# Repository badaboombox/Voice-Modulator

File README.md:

# Voice Modulator

The original project contains the fully routed 95 x 65 mm board. [PCB layout and checks](PCB_LAYOUT.md)

[JLCPCB quote files](production/README.md) · [Schematic and board screenshots](screenshots/README.md)

**Rev A.2 electrical plan locked for schematic capture — 2026-11-21.**

- [SCHEMATIC_GUIDE.md](SCHEMATIC_GUIDE.md): fixed architecture, six
  sheets, operating modes, power sequencing, layout constraints and acceptance work.
- [IC_CONNECTIONS.md](IC_CONNECTIONS.md): draw one sheet at a time. Pin tables
  list nets; each passive value and connection appears once beside its associated
  component. All 15 IC/protection devices and inter-sheet ports are covered.

The screenshot components remain the foundation. The abbreviated flash ordering
code is resolved to W25Q128JVSIQ; the required speaker amp is PAM8403DR (SOP-16). The added codec,
analog-switch ring modulator, oscillator, flash and protection implement Tiers 2/3
and replay of recorded speech through the analog effect.

| Constraint | Locked decision |
| --- | --- |
| PCB | 95 x 65 mm, four layers, 1.6-mm FR-4 |
| Effect | Analog metallic ring modulation, tone and dry/wet blend |
| Audio | 32 ksample/s, 16-bit; one 10-second dry recording slot |
| Monitoring | Headphones live; armed internal speaker for recorded playback |
| Power | USB 2.0 host-powered, 500-mA configuration |
| Budget | $185 allocation, under-$200 landed-order requirement |

Schematic capture and PCB routing are complete. The project includes the files for a manufacturing estimate. Firmware, hardware validation, and a vendor price remain open.

Rev A.2 retains U6 TLV320AIC3104IRHBR after comparison with AIC3204 and adopts
D1 USBLC6-2SC6 for USB ESD protection, matching the part already in the schematic.

Rev A.2 corrects U12 to the user-specified PAM8403DR already present in KiCad.
Its 16-pin table includes one-channel speaker wiring, input attenuation, VREF
bypass and mute/shutdown control.

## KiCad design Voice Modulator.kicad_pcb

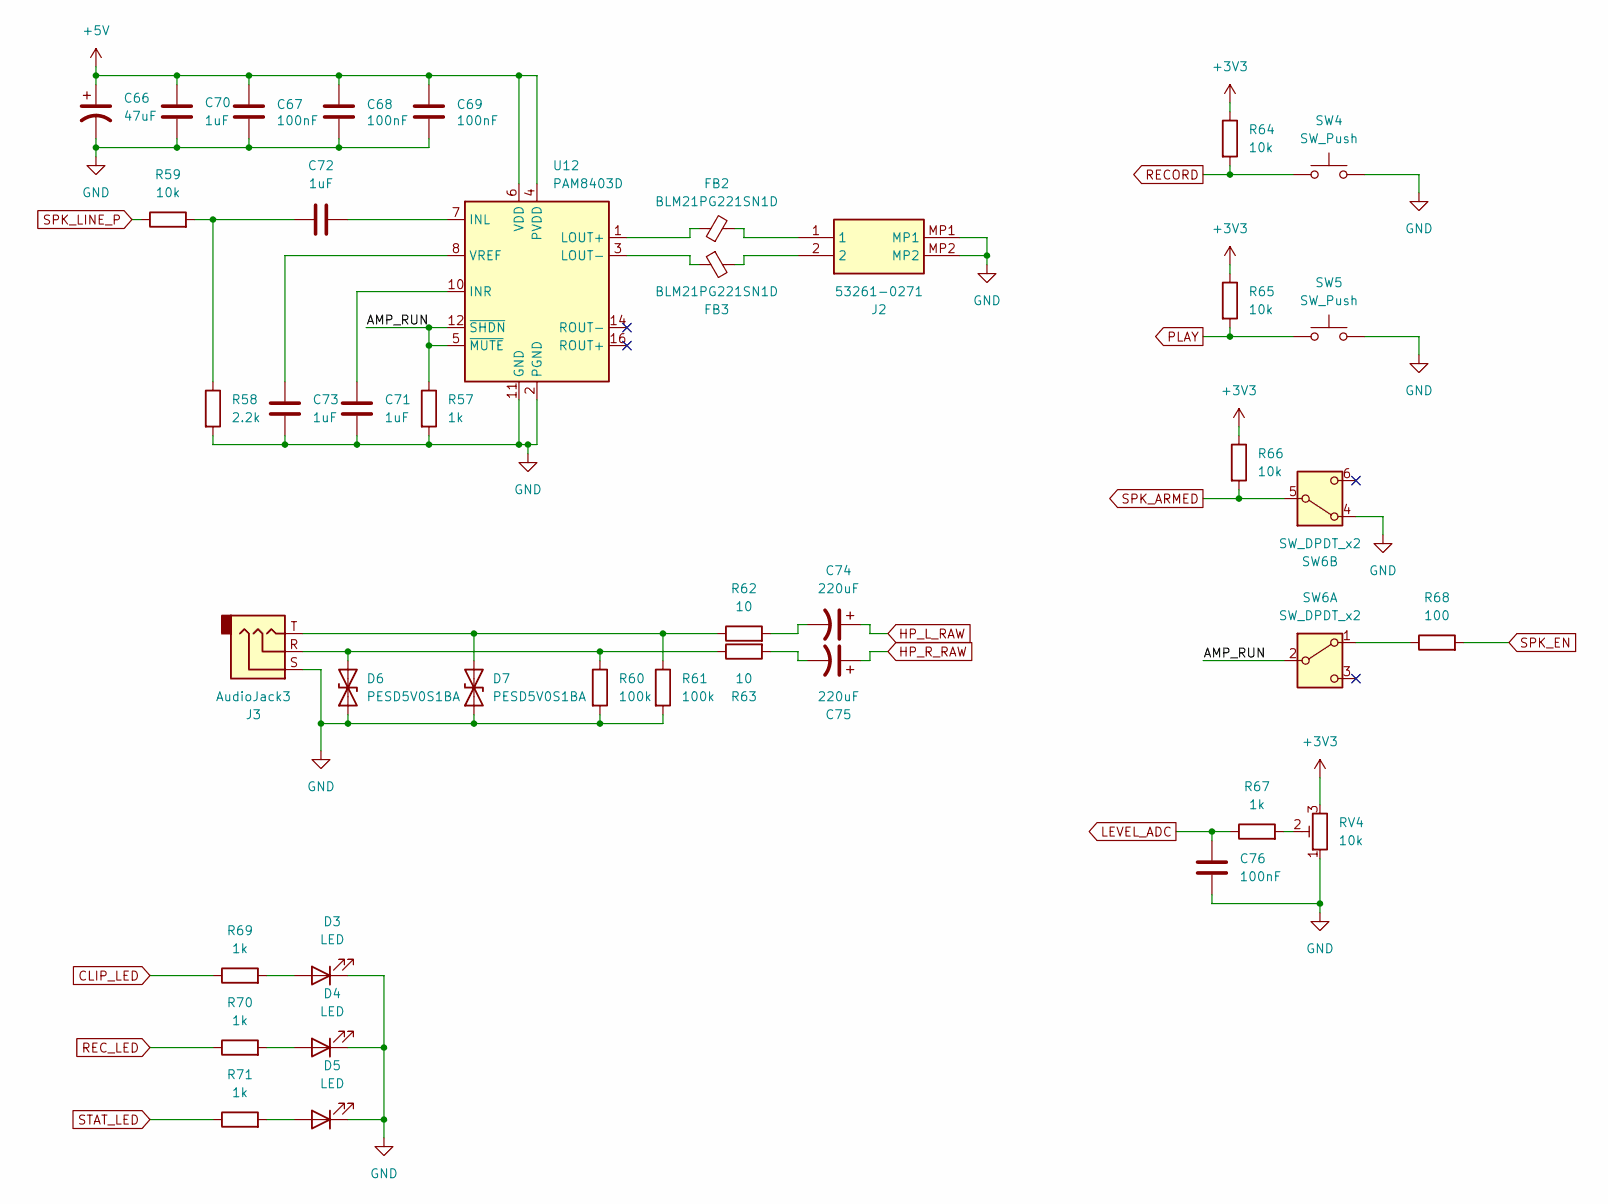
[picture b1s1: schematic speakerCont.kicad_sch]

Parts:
C66: 47uF; CP_Radial_D5.0mm_P2.00mm
C67, C68, C69, C76: 100nF; C_0402_1005Metric
C70, C71, C72, C73: 1uF; C_0805_2012Metric
C74, C75: 220uF; CP_Radial_D6.3mm_P2.50mm
D3, D4, D5: LED; LED_0805_2012Metric
D6, D7: PESD5V0S1BA; D_SOD-323
FB2, FB3: BLM21PG221SN1D; L_0805_2012Metric
J2: 53261-0271; 532610271; Manufacturer_Part_Number 53261-0271; Mouser Part Number 538-53261-0271
J3: AudioJack3; Jack_3.5mm_CUI_SJ-3523-SMT_Horizontal
R57, R67, R69, R70, R71: 1k; R_0402_1005Metric
R58: 2.2k; R_0402_1005Metric
R59, R64, R65, R66: 10k; R_0402_1005Metric
R60, R61: 100k; R_0402_1005Metric
R62, R63: 10; R_0402_1005Metric
R68: 100; R_0402_1005Metric
RV4: 10k; Potentiometer_Bourns_PTV09A-1_Single_Vertical
SW4, SW5: SW_Push; SW_PUSH_6mm_H4.3mm
SW6: SW_DPDT_x2; SW_E-Switch_EG2219_DPDT_Angled
U12: PAM8403D; SOIC-16_3.9x9.9mm_P1.27mm

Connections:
+3V3: R64.1, R65.1, R66.1, RV4.3; also elsewhere on the board
+5V: C66.1, C67.1, C68.1, C69.1, C70.1, U12.4 (PVDD), U12.6 (VDD), U12.13 (PVDD); also elsewhere on the board
/Speaker + Controls/AMP_RUN: R57.1, SW6.2 (B), U12.5 (~MUTE), U12.12 (~SHDN)
CLIP_LED: R69.1; also elsewhere on the board
GND: C66.2, C67.2, C68.2, C69.2, C70.2, C71.2, C73.2, C76.2, D3.1 (K), D4.1 (K), D5.1 (K), D6.1 (A1), D7.1 (A1), J2.MP1, J2.MP2, J3.S, R57.2, R58.2, R60.2, R61.2, RV4.1, SW4.2, SW5.2, SW6.4 (A), U12.2 (PGND), U12.11 (GND), U12.15 (PGND); also elsewhere on the board
HP_L_RAW: C74.1; also elsewhere on the board
HP_R_RAW: C75.1; also elsewhere on the board
LEVEL_ADC: C76.1, R67.1; also elsewhere on the board
unnamed: C72.1, R58.1, R59.2
unnamed: C74.2, R62.2
unnamed: C75.2, R63.2
unnamed: D3.2 (A), R69.2
unnamed: D4.2 (A), R70.2
unnamed: D5.2 (A), R71.2
unnamed: D6.2 (A2), J3.R, R60.1, R63.1
unnamed: D7.2 (A2), J3.T, R61.1, R62.1
unnamed: FB2.2, J2.1
unnamed: FB3.2, J2.2
unnamed: R67.2, RV4.2
unnamed: R68.1, SW6.1 (A)
unnamed: C72.2, U12.7 (INL)
unnamed: C71.1, U12.10 (INR)
unnamed: FB2.1, U12.1 (LOUT+)
unnamed: FB3.1, U12.3 (LOUT-)
unnamed: C73.1, U12.8 (VREF)
PLAY: R65.2, SW5.1; also elsewhere on the board
RECORD: R64.2, SW4.1; also elsewhere on the board
REC_LED: R70.1; also elsewhere on the board
SPK_ARMED: R66.2, SW6.5 (B); also elsewhere on the board
SPK_EN: R68.2; also elsewhere on the board
SPK_LINE_P: R59.1; also elsewhere on the board
STAT_LED: R71.1; also elsewhere on the board

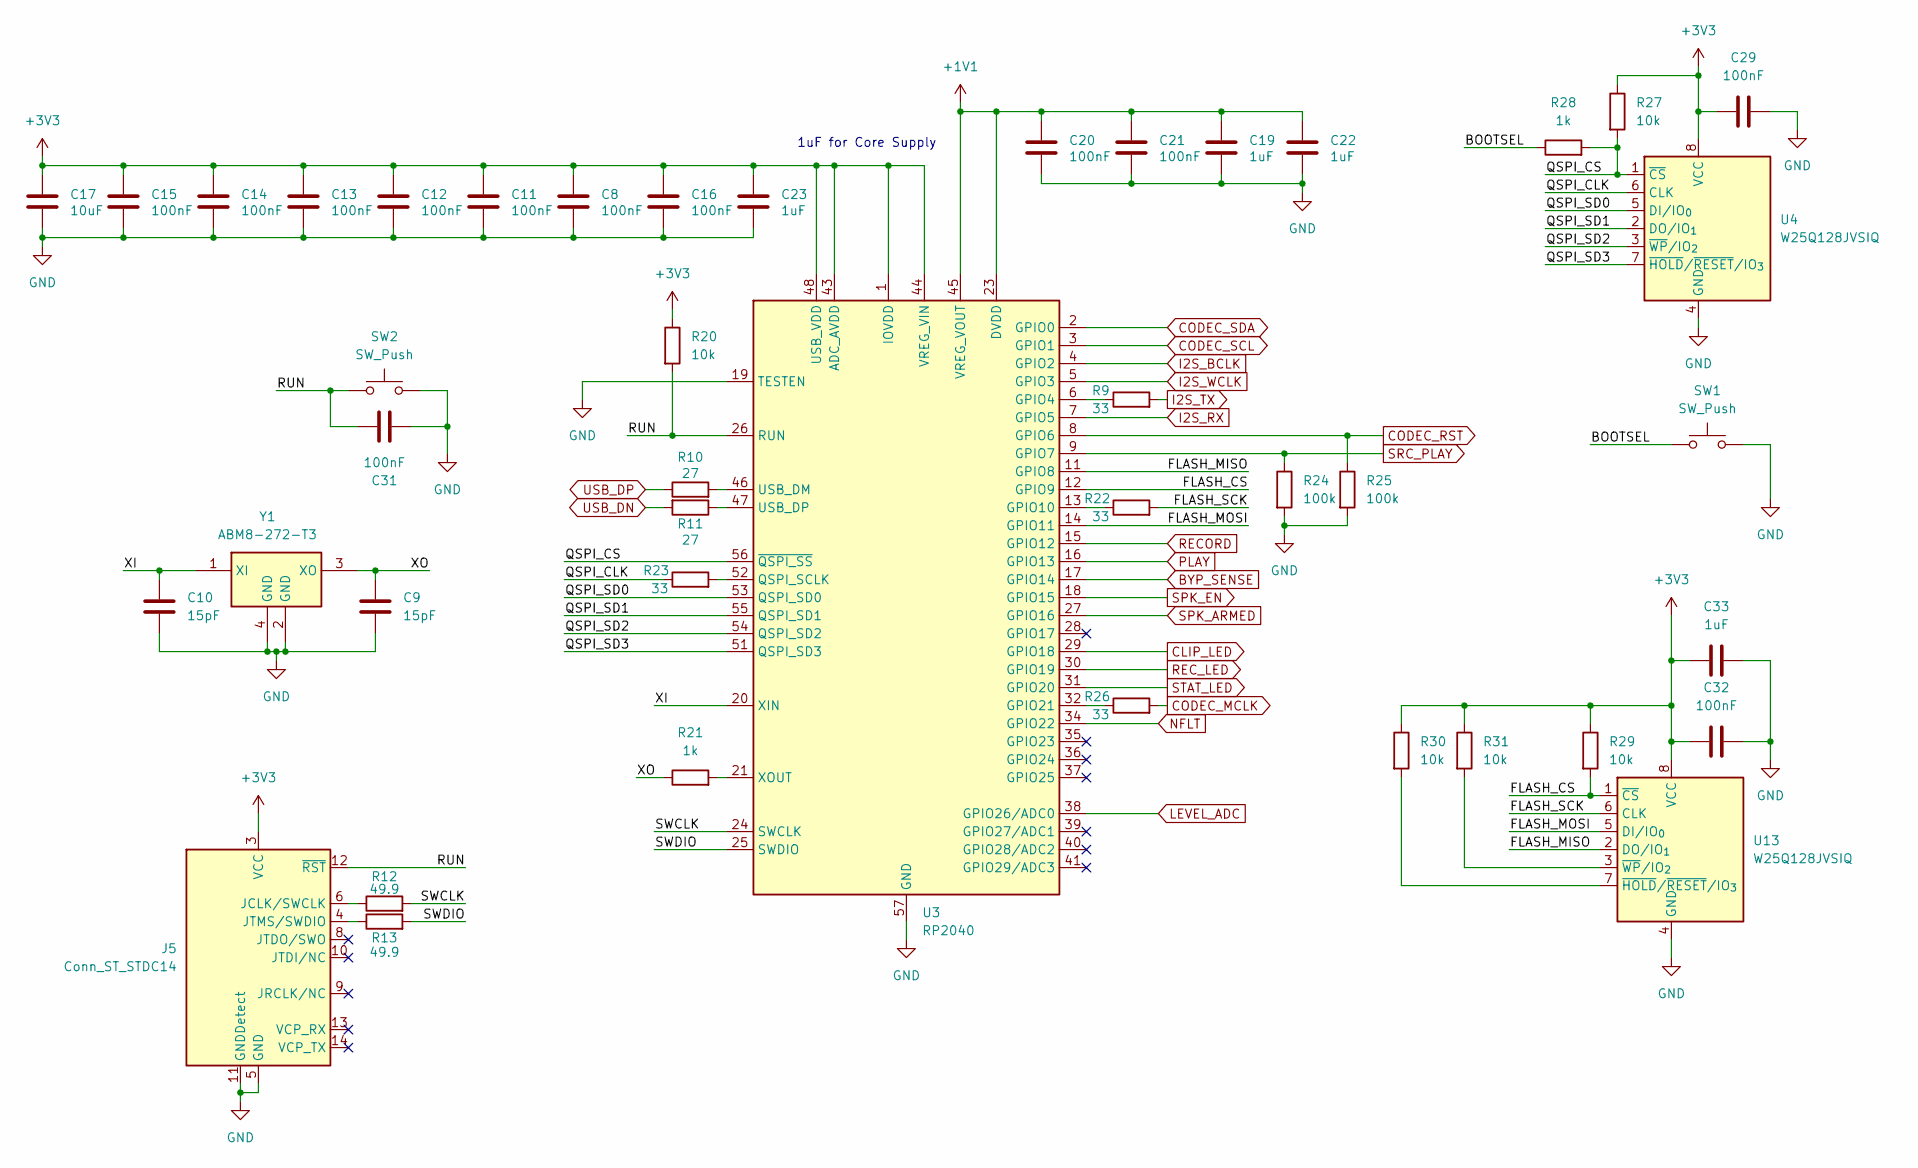
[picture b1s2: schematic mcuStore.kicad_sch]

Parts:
C8, C11, C12, C13, C14, C15, C16, C20, C21, C29, C31, C32: 100nF; C_0402_1005Metric
C9, C10: 15pF; C_0402_1005Metric
C17: 10uF; C_1206_3216Metric
C19, C22, C23, C33: 1uF; C_0805_2012Metric
J5: Conn_ST_STDC14; PinHeader_2x07_P1.27mm_Vertical
R9, R22, R23, R26: 33; R_0402_1005Metric
R10, R11: 27; R_0402_1005Metric
R12, R13: 49.9; R_0402_1005Metric
R20, R27, R29, R30, R31: 10k; R_0402_1005Metric
R21, R28: 1k; R_0402_1005Metric
R24, R25: 100k; R_0402_1005Metric
SW1, SW2: SW_Push; SW_PUSH_6mm_H4.3mm
U3: RP2040; QFN-56-1EP_7x7mm_P0.4mm_EP3.2x3.2mm
U4, U13: W25Q128JVSIQ; SOIC-8_5.3x5.3mm_P1.27mm
Y1: ABM8-272-T3; ABM8272T3; Manufacturer_Part_Number ABM8-272-T3; Mouser Part Number 815-ABM8-272-T3

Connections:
+1V1: C19.1, C20.1, C21.1, C22.1, U3.23 (DVDD), U3.45 (VREG_VOUT), U3.50 (DVDD)
+3V3: C8.1, C11.1, C12.1, C13.1, C14.1, C15.1, C16.1, C17.1, C23.1, C29.1, C32.1, C33.1, J5.3 (VCC), R20.1, R27.1, R29.1, R30.1, R31.1, U3.1 (IOVDD), U3.10 (IOVDD), U3.22 (IOVDD), U3.33 (IOVDD), U3.42 (IOVDD), U3.43 (ADC_AVDD), U3.44 (VREG_VIN), U3.48 (USB_VDD), U3.49 (IOVDD), U4.8 (VCC), U13.8 (VCC); also elsewhere on the board
/MCU + Storage/BOOTSEL: R28.1, SW1.1
/MCU + Storage/FLASH_CS: R29.2, U3.12 (GPIO9), U13.1 (~CS)
/MCU + Storage/FLASH_MISO: U3.11 (GPIO8), U13.2 (DO/IO_{1})
/MCU + Storage/FLASH_MOSI: U3.14 (GPIO11), U13.5 (DI/IO_{0})
/MCU + Storage/FLASH_SCK: R22.2, U13.6 (CLK)
/MCU + Storage/QSPI_CLK: R23.1, U4.6 (CLK)
/MCU + Storage/QSPI_CS: R27.2, R28.2, U3.56 (~QSPI_SS), U4.1 (~CS)
/MCU + Storage/QSPI_SD0: U3.53 (QSPI_SD0), U4.5 (DI/IO_{0})
/MCU + Storage/QSPI_SD1: U3.55 (QSPI_SD1), U4.2 (DO/IO_{1})
/MCU + Storage/QSPI_SD2: U3.54 (QSPI_SD2), U4.3 (~WP/IO_{2})
/MCU + Storage/QSPI_SD3: U3.51 (QSPI_SD3), U4.7 (~HOLD/~RESET/IO_{3})
/MCU + Storage/RUN: C31.1, J5.12 (~RST), R20.2, SW2.1, U3.26 (RUN)
/MCU + Storage/SWCLK: R12.2, U3.24 (SWCLK)
/MCU + Storage/SWDIO: R13.2, U3.25 (SWDIO)
/MCU + Storage/XI: C10.1, U3.20 (XIN), Y1.1 (XI)
/MCU + Storage/XO: C9.1, R21.1, Y1.3 (XO)
BYP_SENSE: U3.17 (GPIO14); also elsewhere on the board
CLIP_LED: U3.29 (GPIO18); also elsewhere on the board
CODEC_MCLK: R26.2; also elsewhere on the board
CODEC_RST: R25.1, U3.8 (GPIO6); also elsewhere on the board
CODEC_SCL: U3.3 (GPIO1); also elsewhere on the board
CODEC_SDA: U3.2 (GPIO0); also elsewhere on the board
GND: C8.2, C9.2, C10.2, C11.2, C12.2, C13.2, C14.2, C15.2, C16.2, C17.2, C19.2, C20.2, C21.2, C22.2, C23.2, C29.2, C31.2, C32.2, C33.2, J5.5 (GND), J5.7 (GND), J5.11 (GNDDetect), R24.2, R25.2, SW1.2, SW2.2, U3.19 (TESTEN), U3.57 (GND), U4.4 (GND), U13.4 (GND), Y1.2 (GND), Y1.4 (GND); also elsewhere on the board
I2S_BCLK: U3.4 (GPIO2); also elsewhere on the board
I2S_RX: U3.7 (GPIO5); also elsewhere on the board
I2S_TX: R9.2; also elsewhere on the board
I2S_WCLK: U3.5 (GPIO3); also elsewhere on the board
LEVEL_ADC: U3.38 (GPIO26/ADC0); also elsewhere on the board
NFLT: U3.34 (GPIO22); also elsewhere on the board
unnamed: J5.6 (JCLK/SWCLK), R12.1
unnamed: J5.4 (JTMS/SWDIO), R13.1
unnamed: R9.1, U3.6 (GPIO4)
unnamed: R22.1, U3.13 (GPIO10)
unnamed: R26.1, U3.32 (GPIO21)
unnamed: R23.2, U3.52 (QSPI_SCLK)
unnamed: R10.2, U3.46 (USB_DM)
unnamed: R11.1, U3.47 (USB_DP)
unnamed: R21.2, U3.21 (XOUT)
unnamed: R30.2, U13.7 (~HOLD/~RESET/IO_{3})
unnamed: R31.2, U13.3 (~WP/IO_{2})
PLAY: U3.16 (GPIO13); also elsewhere on the board
RECORD: U3.15 (GPIO12); also elsewhere on the board
REC_LED: U3.30 (GPIO19); also elsewhere on the board
SPK_ARMED: U3.27 (GPIO16); also elsewhere on the board
SPK_EN: U3.18 (GPIO15); also elsewhere on the board
SRC_PLAY: R24.1, U3.9 (GPIO7); also elsewhere on the board
STAT_LED: U3.31 (GPIO20); also elsewhere on the board
USB_DN: R11.2; also elsewhere on the board
USB_DP: R10.1; also elsewhere on the board

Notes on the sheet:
1uF for Core Supply

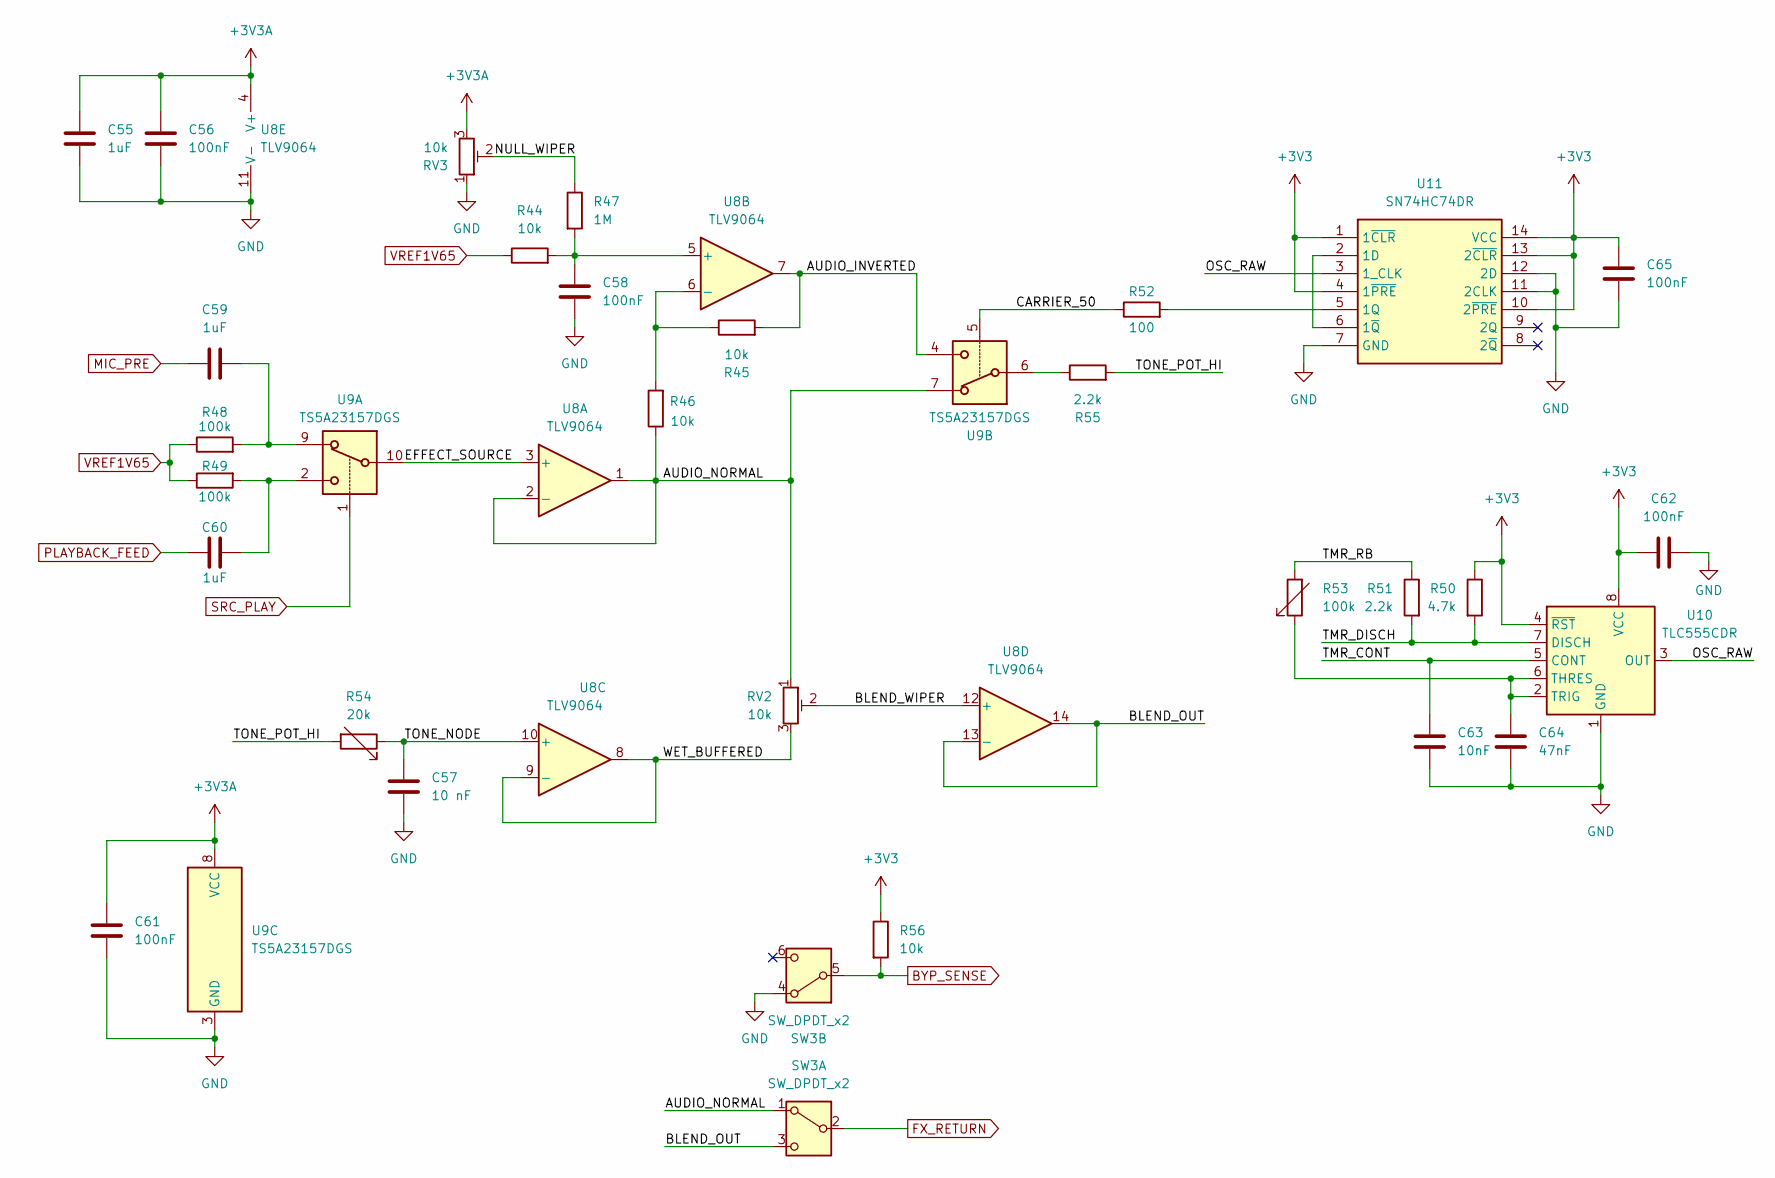
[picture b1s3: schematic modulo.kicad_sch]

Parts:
C55, C59, C60: 1uF; C_0805_2012Metric
C56, C58, C61, C62, C65: 100nF; C_0402_1005Metric
C57: 10 nF; C_0402_1005Metric
C63: 10nF; C_0402_1005Metric
C64: 47nF; C_0402_1005Metric
R44, R45, R46, R56: 10k; R_0402_1005Metric
R47: 1M; R_0402_1005Metric
R48, R49: 100k; R_0402_1005Metric
R50: 4.7k; R_0402_1005Metric
R51, R55: 2.2k; R_0402_1005Metric
R52: 100; R_0402_1005Metric
R53: 100k; Potentiometer_Bourns_PTV09A-1_Single_Vertical
R54: 20k; Potentiometer_Bourns_PTV09A-1_Single_Vertical
RV2: 10k; Potentiometer_Bourns_PTV09A-1_Single_Vertical
RV3: 10k; Potentiometer_Bourns_3296W_Vertical
SW3: SW_DPDT_x2; SW_E-Switch_EG2219_DPDT_Angled
U8: TLV9064; TSSOP-14_4.4x5mm_P0.65mm
U9: TS5A23157DGS; TSSOP-10_3x3mm_P0.5mm
U10: TLC555CDR; SOIC-8_3.9x4.9mm_P1.27mm
U11: SN74HC74DR; SOIC-14_3.9x8.7mm_P1.27mm; Manufacturer_Part_Number SN74HC74DR; Mouser Part Number 595-SN74HC74DR

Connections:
+3V3: C62.2, C65.1, R50.1, R56.1, U10.4 (~RST), U10.8 (VCC), U11.1 (1~CLR), U11.4 (1~PRE), U11.10 (2~PRE), U11.13 (2~CLR), U11.14 (VCC); also elsewhere on the board
+3V3A: C55.1, C56.1, C61.2, RV3.3, U8.4 (V+), U9.8 (VCC); also elsewhere on the board
/Modulation/AUDIO_INVERTED: R45.2, U8.7, U9.4
/Modulation/AUDIO_NORMAL: R46.1, RV2.1, SW3.1 (A), U8.1, U8.2 (-), U9.7
/Modulation/BLEND_OUT: SW3.3 (C), U8.13 (-), U8.14
/Modulation/BLEND_WIPER: RV2.2, U8.12 (+)
/Modulation/CARRIER_50: R52.1, U9.5
/Modulation/EFFECT_SOURCE: U8.3 (+), U9.10
/Modulation/NULL_WIPER: R47.1, RV3.2
/Modulation/OSC_RAW: U10.3 (OUT), U11.3 (1_CLK)
/Modulation/TMR_CONT: C63.2, U10.5 (CONT)
/Modulation/TMR_DISCH: R50.2, R51.2, U10.7 (DISCH)
/Modulation/TMR_RB: R51.1, R53.2
/Modulation/TONE_NODE: C57.1, R54.1, U8.10 (+)
/Modulation/TONE_POT_HI: R54.2, R55.2
/Modulation/WET_BUFFERED: RV2.3, U8.8, U8.9 (-)
BYP_SENSE: R56.2, SW3.5 (B); also elsewhere on the board
FX_RETURN: SW3.2 (B); also elsewhere on the board
GND: C55.2, C56.2, C57.2, C58.1, C61.1, C62.1, C63.1, C64.1, C65.2, RV3.1, SW3.4 (A), U8.11 (V-), U9.3 (GND), U10.1 (GND), U11.7 (GND), U11.11 (2CLK), U11.12 (2D); also elsewhere on the board
MIC_PRE: C59.1; also elsewhere on the board
unnamed: C59.2, R48.2, U9.9
unnamed: C60.2, R49.2, U9.2
unnamed: R55.1, U9.6
unnamed: C58.2, R44.2, R47.2, U8.5 (+)
unnamed: R45.1, R46.2, U8.6 (-)
unnamed: C64.2, R53.1, U10.2 (TRIG), U10.6 (THRES)
unnamed: U11.2 (1D), U11.6 (1~Q)
unnamed: R52.2, U11.5 (1Q)
PLAYBACK_FEED: C60.1; also elsewhere on the board
SRC_PLAY: U9.1; also elsewhere on the board
VREF1V65: R44.1, R48.1, R49.1; also elsewhere on the board

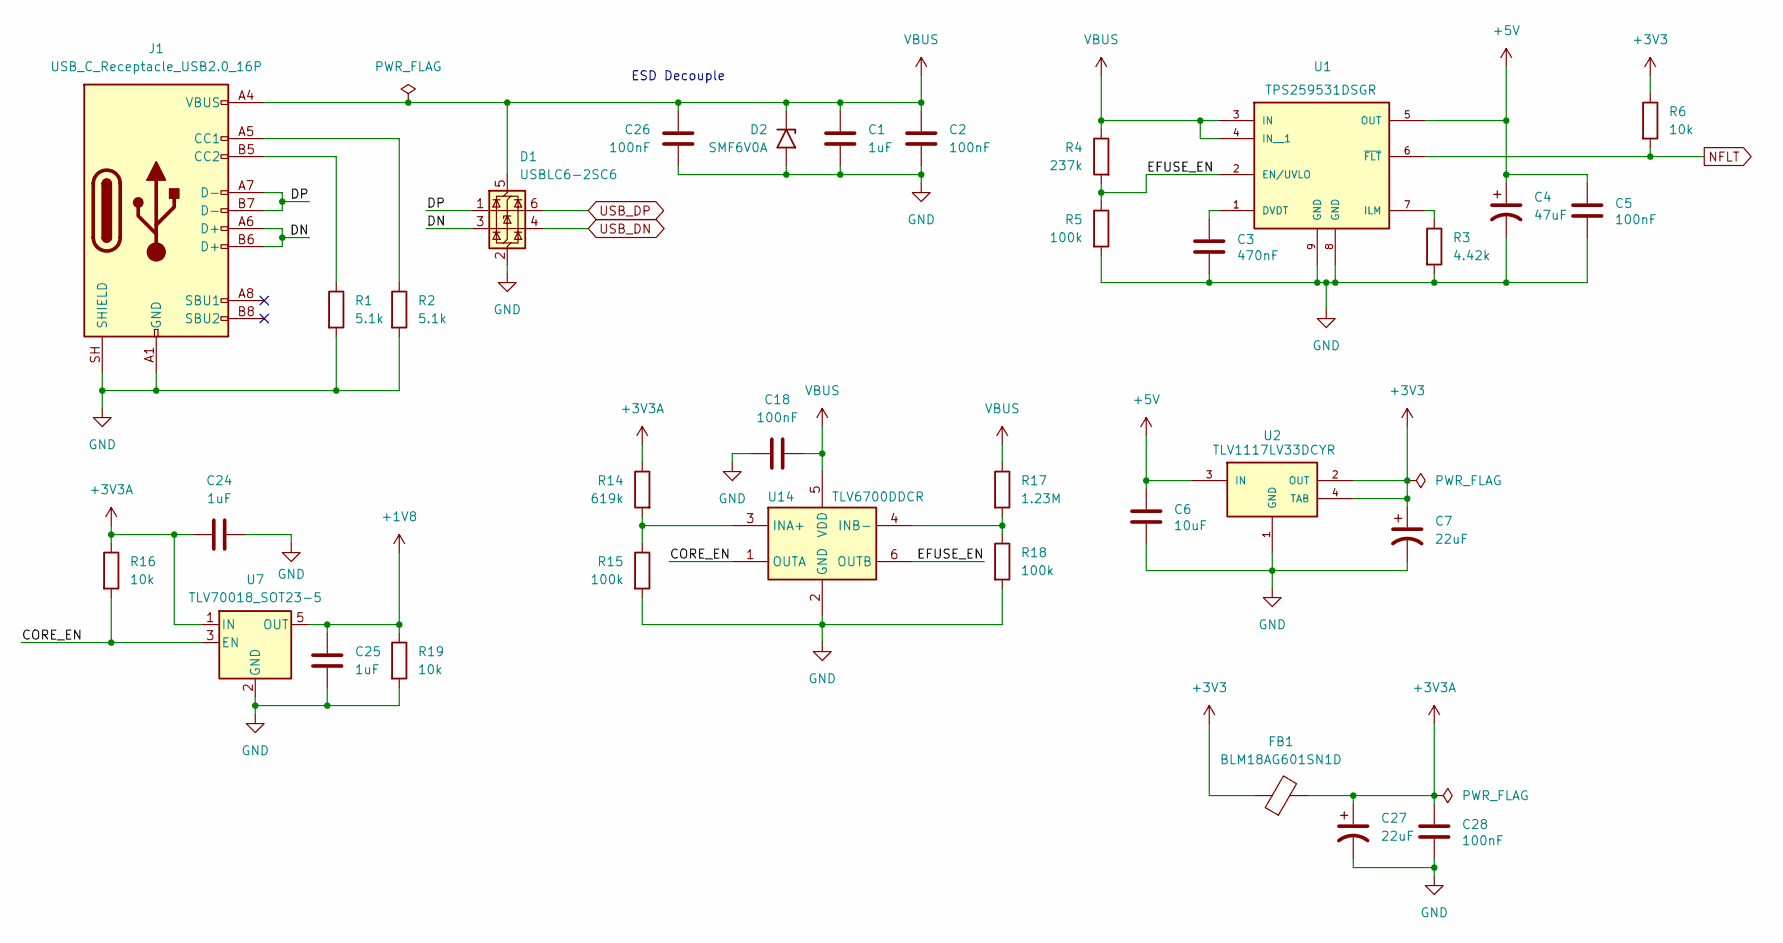
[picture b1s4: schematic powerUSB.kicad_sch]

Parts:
C1, C24, C25: 1uF; C_0805_2012Metric
C2, C5, C18, C26, C28: 100nF; C_0402_1005Metric
C3: 470nF; C_0402_1005Metric
C4: 47uF; CP_Radial_D5.0mm_P2.00mm
C6: 10uF; C_1206_3216Metric
C7, C27: 22uF; C_Rect_L7.0mm_W4.5mm_P5.00mm
D1: USBLC6-2SC6; SOT-23-6
D2: SMF6V0A; D_SMF
FB1: BLM18AG601SN1D; L_0603_1608Metric
J1: USB_C_Receptacle_USB2.0_16P; USB_C_Receptacle_GCT_USB4105-xx-A_16P_TopMnt_Horizontal
R1, R2: 5.1k; R_0402_1005Metric
R3: 4.42k; R_0402_1005Metric
R4: 237k; R_0402_1005Metric
R5, R15, R18: 100k; R_0402_1005Metric
R6, R16, R19: 10k; R_0402_1005Metric
R14: 619k; R_0402_1005Metric
R17: 1.23M; R_0402_1005Metric
U1: TPS259531DSGR; DFN-8-1EP_2x2mm_P0.5mm_EP0.9x1.6mm; MPN TPS259531DSGR
U2: TLV1117LV33DCYR; VREG_TLV1117LV33DCYR; MPN TLV1117LV33DCYR
U7: TLV70018_SOT23-5; SOT-23-5
U14: TLV6700DDCR; SOT95P280X110-6N; Manufacturer_Part_Number TLV6700DDCR; Mouser Part Number 595-TLV6700DDCR

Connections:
+1V8: C25.2, R19.1, U7.5 (OUT); also elsewhere on the board
+3V3: C7.1, FB1.1, R6.1, U2.2 (OUT), U2.4 (TAB); also elsewhere on the board
+3V3A: C24.1, C27.1, C28.1, FB1.2, R14.1, R16.1, U7.1 (IN); also elsewhere on the board
+5V: C4.1, C5.1, C6.1, U1.5 (OUT), U2.3 (IN); also elsewhere on the board
/Power + USB/CORE_EN: R16.2, U7.3 (EN), U14.1 (OUTA)
/Power + USB/DN: D1.3 (I/O2), J1.A6 (D+), J1.B6 (D+)
/Power + USB/DP: D1.1 (I/O1), J1.A7 (D-), J1.B7 (D-)
/Power + USB/EFUSE_EN: R4.2, R5.1, U1.2 (EN/UVLO), U14.6 (OUTB)
GND: C1.2, C2.2, C3.2, C4.2, C5.2, C6.2, C7.2, C18.1, C24.2, C25.1, C26.2, C27.2, C28.2, D1.2 (GND), D2.2 (A2), J1.A1 (GND), J1.A12 (GND), J1.B1 (GND), J1.B12 (GND), J1.SH (SHIELD), R1.2, R2.2, R3.2, R5.2, R15.2, R18.2, R19.2, U1.8 (GND), U1.9 (GND), U2.1 (GND), U7.2 (GND), U14.2 (GND); also elsewhere on the board
NFLT: R6.2, U1.6 (~FLT); also elsewhere on the board
unnamed: J1.A5 (CC1), R2.1
unnamed: J1.B5 (CC2), R1.1
unnamed: C3.1, U1.1 (DVDT)
unnamed: R3.1, U1.7 (ILM)
unnamed: R14.2, R15.1, U14.3 (INA+)
unnamed: R17.2, R18.1, U14.4 (INB-)
USB_DN: D1.4 (I/O2); also elsewhere on the board
USB_DP: D1.6 (I/O1); also elsewhere on the board
VBUS: C1.1, C2.1, C18.2, C26.1, D1.5 (VBUS), D2.1 (A1), J1.A4 (VBUS), J1.A9 (VBUS), J1.B4 (VBUS), J1.B9 (VBUS), R4.1, R17.1, U1.3 (IN), U1.4 (IN__1), U14.5 (VDD)

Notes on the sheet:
ESD Decouple

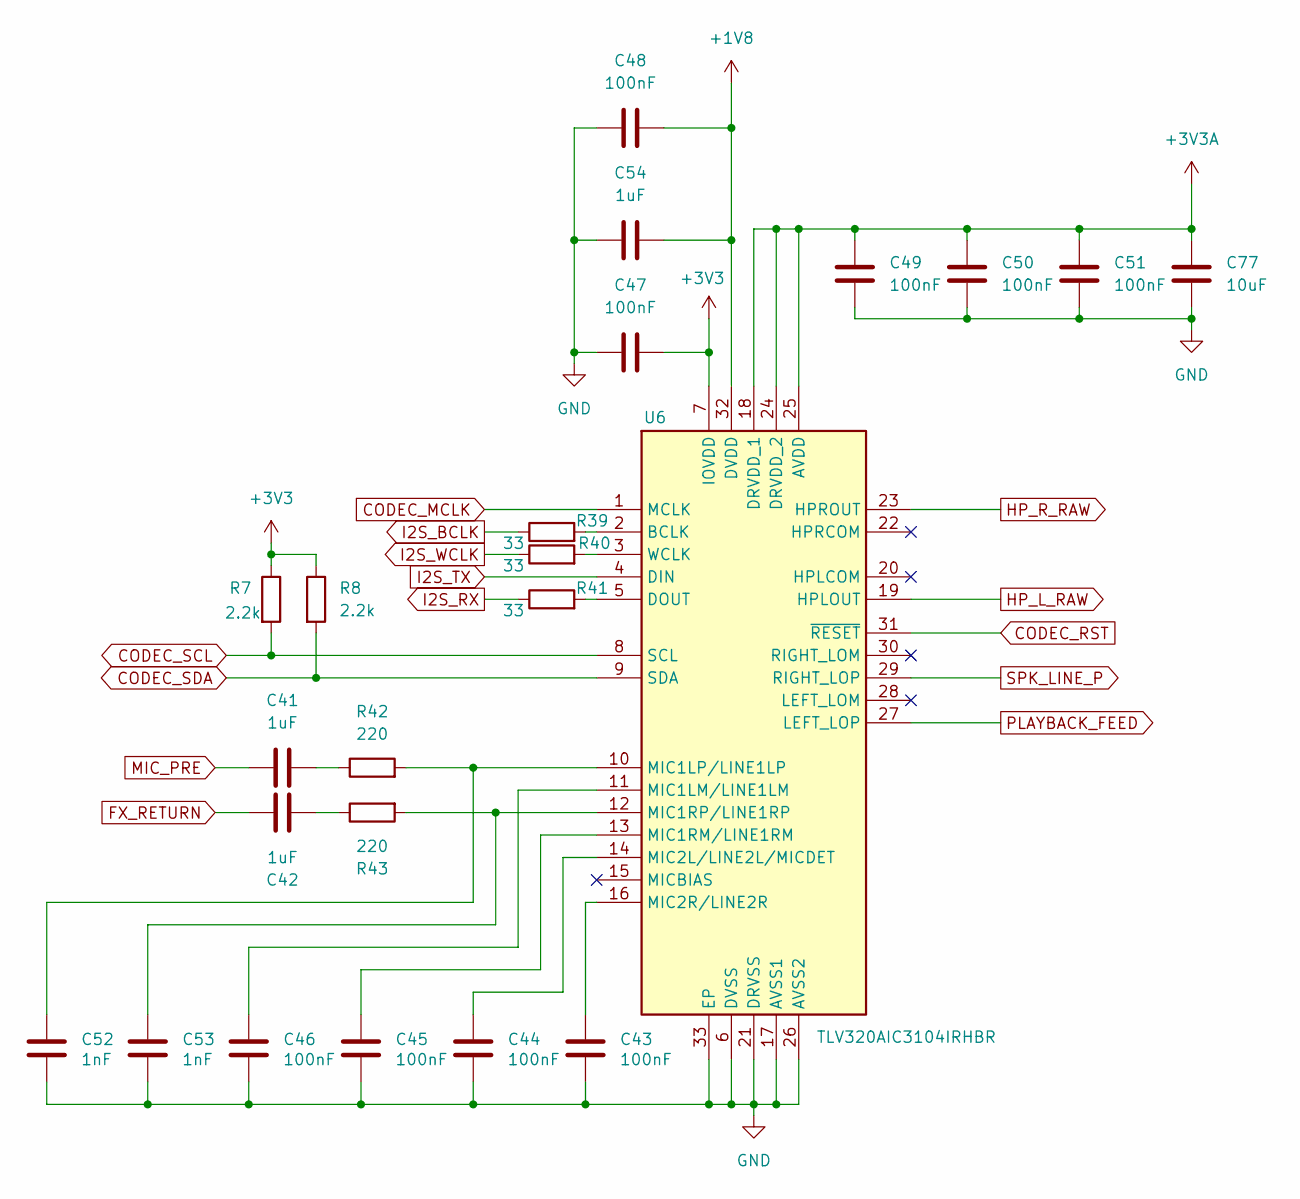
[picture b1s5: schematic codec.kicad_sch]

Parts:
C41, C42, C54: 1uF; C_0805_2012Metric
C43, C44, C45, C46, C47, C48, C49, C50, C51: 100nF; C_0402_1005Metric
C52, C53: 1nF; C_0402_1005Metric
C77: 10uF; C_1206_3216Metric
R7, R8: 2.2k; R_0402_1005Metric
R39, R40, R41: 33; R_0402_1005Metric
R42, R43: 220; R_0402_1005Metric
U6: TLV320AIC3104IRHBR; QFN50P500X500X100-33N-D; Manufacturer_Part_Number TLV320AIC3104IRHBR; Mouser Part Number 595-TLV320C3104IRHBR

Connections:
+1V8: C48.2, C54.1, U6.32 (DVDD); also elsewhere on the board
+3V3: C47.2, R7.1, R8.1, U6.7 (IOVDD); also elsewhere on the board
+3V3A: C49.2, C50.2, C51.2, C77.1, U6.18 (DRVDD_1), U6.24 (DRVDD_2), U6.25 (AVDD); also elsewhere on the board
CODEC_MCLK: U6.1 (MCLK); also elsewhere on the board
CODEC_RST: U6.31 (~RESET); also elsewhere on the board
CODEC_SCL: R7.2, U6.8 (SCL); also elsewhere on the board
CODEC_SDA: R8.2, U6.9 (SDA); also elsewhere on the board
FX_RETURN: C42.1; also elsewhere on the board
GND: C43.2, C44.2, C45.2, C46.2, C47.1, C48.1, C49.1, C50.1, C51.1, C52.2, C53.2, C54.2, C77.2, U6.6 (DVSS), U6.17 (AVSS1), U6.21 (DRVSS), U6.26 (AVSS2), U6.33 (EP); also elsewhere on the board
HP_L_RAW: U6.19 (HPLOUT); also elsewhere on the board
HP_R_RAW: U6.23 (HPROUT); also elsewhere on the board
I2S_BCLK: R39.1; also elsewhere on the board
I2S_RX: R41.1; also elsewhere on the board
I2S_TX: U6.4 (DIN); also elsewhere on the board
I2S_WCLK: R40.1; also elsewhere on the board
MIC_PRE: C41.1; also elsewhere on the board
unnamed: C41.2, R42.1
unnamed: C42.2, R43.1
unnamed: R39.2, U6.2 (BCLK)
unnamed: R41.2, U6.5 (DOUT)
unnamed: C46.1, U6.11 (MIC1LM/LINE1LM)
unnamed: C52.1, R42.2, U6.10 (MIC1LP/LINE1LP)
unnamed: C45.1, U6.13 (MIC1RM/LINE1RM)
unnamed: C53.1, R43.2, U6.12 (MIC1RP/LINE1RP)
unnamed: C44.1, U6.14 (MIC2L/LINE2L/MICDET)
unnamed: C43.1, U6.16 (MIC2R/LINE2R)
unnamed: R40.2, U6.3 (WCLK)
PLAYBACK_FEED: U6.27 (LEFT_LOP); also elsewhere on the board
SPK_LINE_P: U6.29 (RIGHT_LOP); also elsewhere on the board

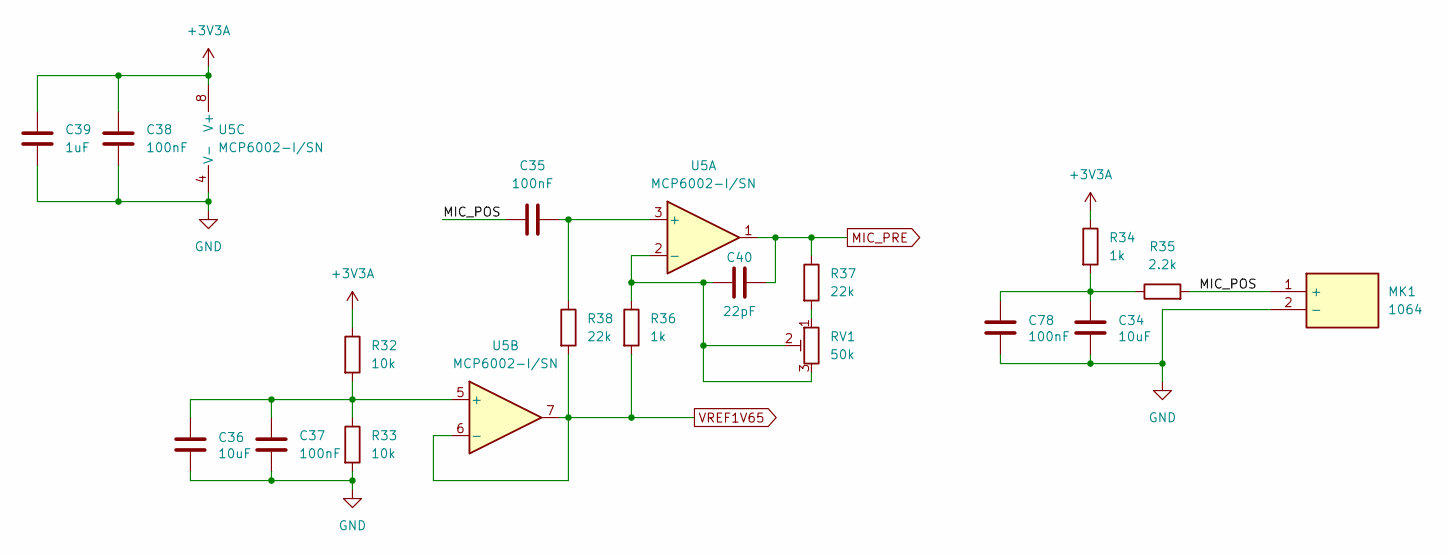
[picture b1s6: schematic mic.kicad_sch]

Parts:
C34, C36: 10uF; C_1206_3216Metric
C35, C37, C38, C78: 100nF; C_0402_1005Metric
C39: 1uF; C_0805_2012Metric
C40: 22pF; C_0402_1005Metric
MK1: 1064; Manufacturer_Part_Number 1064; Mouser Part Number 485-1064
R32, R33: 10k; R_0402_1005Metric
R34, R36: 1k; R_0402_1005Metric
R35: 2.2k; R_0402_1005Metric
R37, R38: 22k; R_0402_1005Metric
RV1: 50k; Potentiometer_Bourns_3296W_Vertical
U5: MCP6002-I/SN; SOIC-8_3.9x4.9mm_P1.27mm

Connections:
+3V3A: C38.1, C39.1, R32.1, R34.1, U5.8 (V+); also elsewhere on the board
/Microphone/MIC_POS: C35.1, MK1.1 (+), R35.2
GND: C34.2, C36.2, C37.1, C38.2, C39.2, C78.2, MK1.2 (-), R33.2, U5.4 (V-); also elsewhere on the board
MIC_PRE: C40.2, R37.1, U5.1; also elsewhere on the board
unnamed: C34.1, C78.1, R34.2, R35.1
unnamed: R37.2, RV1.1
unnamed: C35.2, R38.1, U5.3 (+)
unnamed: C40.1, R36.1, RV1.2, RV1.3, U5.2 (-)
unnamed: C36.1, C37.2, R32.2, R33.1, U5.5 (+)
VREF1V65: R36.2, R38.2, U5.6 (-), U5.7; also elsewhere on the board

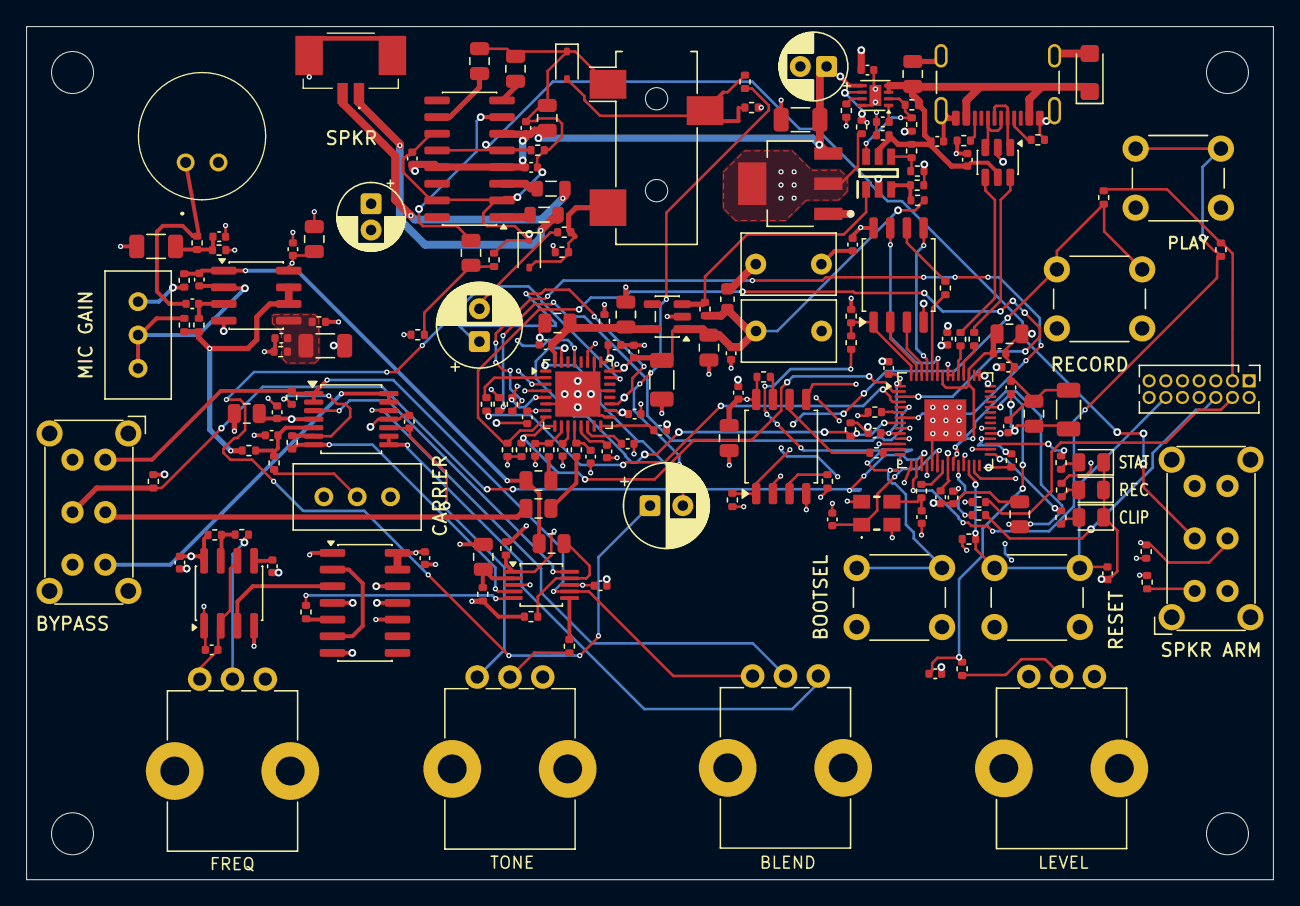
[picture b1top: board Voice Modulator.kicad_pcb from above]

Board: 4 copper layers, 95.0 x 65.0 mm, 192 parts (0 on the bottom side), 129 nets.

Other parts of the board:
H1, H2, H3, H4: M3 mounting; MountingHole_3.2mm_M3

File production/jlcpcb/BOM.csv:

Comment,Designator,Footprint,LCSC Part #,Quantity
1uF CL21B105KAFNNNE,"C1,C19,C22,C23,C24,C25,C33,C39,C41,C42,C54,C55,C59,C60,C70,C71,C72,C73",C_0805_2012Metric,C116352,18
100nF CL05B104KO5NNNC,"C2,C5,C8,C11,C12,C13,C14,C15,C16,C18,C20,C21,C26,C28,C29,C31,C32,C35,C37,C38,C43,C44,C45,C46,C47,C48,C49,C50,C51,C56,C58,C61,C62,C65,C67,C68,C69,C76,C78",C_0402_1005Metric,C1525,39
470nF 0402B474K100CT,C3,C_0402_1005Metric,C2443202,1
47uF EEUFR1E470,"C4,C66",CP_Radial_D5.0mm_P2.00mm,C407893,2
10uF GRM31CR71C106KA12L,"C6,C17,C34,C36,C77",C_1206_3216Metric,C97954,5
22uF FG20X7R1C226MRT00,"C7,C27",C_Rect_L7.0mm_W4.5mm_P5.00mm,C3694690,2
15pF VJ0402A150FLAAJ32,"C9,C10",C_0402_1005Metric,C1514440,2
22pF 0402CG220J500NT,C40,C_0402_1005Metric,C1555,1
1nF CL05C102JB5NNNC,"C52,C53",C_0402_1005Metric,C307441,2
10 nF GRM1555C1H103JE01D,C57,C_0402_1005Metric,C22400107,1
10nF CL05B103KB5NNNC,C63,C_0402_1005Metric,C15195,1
47nF GRM155R71E473JA88D,C64,C_0402_1005Metric,C437528,1
220uF EEUFR1A221,"C74,C75",CP_Radial_D6.3mm_P2.50mm,C407869,2
USBLC6-2SC6,D1,SOT-23-6,C7519,1
SMF6V0A SMF6V0A-HM3-18,D2,D_SMF,C1979297,1
LED 17-21SURC/S530-A3/TR8,"D3,D4",LED_0805_2012Metric,C72037,2
LED KT-0805G,D5,LED_0805_2012Metric,C2297,1
"PESD5V0S1BA PESD5V0S1BA,115","D6,D7",D_SOD-323,C19224,2
BLM18AG601SN1D,FB1,L_0603_1608Metric,C19330,1
BLM21PG221SN1D,"FB2,FB3",L_0805_2012Metric,C85840,2
USB_C_Receptacle_USB2.0_16P USB4105-GF-A,J1,USB_C_Receptacle_GCT_USB4105-xx-A_16P_TopMnt_Horizontal,C3020560,1
53261-0271,J2,532610271,C177225,1
AudioJack3 SJ-3523-SMT-TR,J3,Jack_3.5mm_CUI_SJ-3523-SMT_Horizontal,C4991872,1
Conn_ST_STDC14 PZ127-2-07-Z,J5,PinHeader_2x07_P1.27mm_Vertical,C5372811,1
1064 CMA-4544PF-W,MK1,1064,C3273770,1
5.1k 0402WGF5101TCE,"R1,R2",R_0402_1005Metric,C25905,2
4.42k RC0402FR-074K42L,R3,R_0402_1005Metric,C137967,1
237k RC0402FR-07237KP,R4,R_0402_1005Metric,C6263572,1
100k 0402WGF1003TCE,"R5,R24,R25,R48,R49,R60,R61",R_0402_1005Metric,C25741,7
10k 0402WGF1002TCE,"R6,R16,R19,R20,R27,R29,R30,R31,R32,R33,R44,R56,R59,R64,R65,R66",R_0402_1005Metric,C25744,16
2.2k RC0402FR-072K2L,"R7,R8,R35,R51,R55,R58",R_0402_1005Metric,C114762,6
33 0402WGF330JTCE,"R9,R22,R23,R26,R39,R40,R41",R_0402_1005Metric,C25105,7
27 0402WGF270JTCE,"R10,R11",R_0402_1005Metric,C25100,2
49.9 RC0402FR-0749R9L,"R12,R13",R_0402_1005Metric,C87044,2
619k RE0402BRE07619KL,R14,R_0402_1005Metric,C7042129,1
100k ERA2AEB104X,"R15,R18",R_0402_1005Metric,C445619,2
1.23M 0.1% 0402,R17,R_0402_1005Metric,,1
1k 0402WGF1001TCE,"R21,R28,R34,R36,R57,R67,R69,R70,R71",R_0402_1005Metric,C11702,9
22k RC0402FR-0722KL,"R37,R38",R_0402_1005Metric,C82868,2
220 0402WGF2200TCE,"R42,R43",R_0402_1005Metric,C25091,2
10k RT0402BRD0710KL,"R45,R46",R_0402_1005Metric,C190095,2
1M 0402WGF1004TCE,R47,R_0402_1005Metric,C26083,1
4.7k 0402WGF4701TCE,R50,R_0402_1005Metric,C25900,1
100 0402WGF1000TCE,"R52,R68",R_0402_1005Metric,C25076,2
Bourns PTV09A-1 100k linear no detent,R53,Potentiometer_Bourns_PTV09A-1_Single_Vertical,,1
Bourns PTV09A-1 20k linear no detent,R54,Potentiometer_Bourns_PTV09A-1_Single_Vertical,,1
10 RC0402FR-0710RL,"R62,R63",R_0402_1005Metric,C138066,2
50k 3296W-1-503LF,RV1,Potentiometer_Bourns_3296W_Vertical,C83686,1
Bourns PTV09A-1 10k linear no detent,"RV2,RV4",Potentiometer_Bourns_PTV09A-1_Single_Vertical,,2
10k 3296W-1-103LF,RV3,Potentiometer_Bourns_3296W_Vertical,C34846,1
SW_Push PTS645SL43-2LFS,"SW1,SW2,SW4,SW5",SW_PUSH_6mm_H4.3mm,C285482,4
SW_DPDT_x2 EG2219,"SW3,SW6",SW_E-Switch_EG2219_DPDT_Angled,C3664594,2
TPS259531DSGR,U1,DFN-8-1EP_2x2mm_P0.5mm_EP0.9x1.6mm,C2155674,1
TLV1117LV33DCYR,U2,VREG_TLV1117LV33DCYR,C15578,1
RP2040,U3,QFN-56-1EP_7x7mm_P0.4mm_EP3.2x3.2mm,C2040,1
W25Q128JVSIQ,"U4,U13",SOIC-8_5.3x5.3mm_P1.27mm,C2613931,2
MCP6002-I/SN,U5,SOIC-8_3.9x4.9mm_P1.27mm,C116706,1
TLV320AIC3104IRHBR,U6,QFN50P500X500X100-33N-D,C181753,1
TLV70018_SOT23-5 TLV70018DDCR,U7,SOT-23-5,C79924,1
TLV9064 TLV9064IPWR,U8,TSSOP-14_4.4x5mm_P0.65mm,C779410,1
TS5A23157DGS TS5A23157DGSR,U9,TSSOP-10_3x3mm_P0.5mm,C11133,1
TLC555CDR,U10,SOIC-8_3.9x4.9mm_P1.27mm,C6986,1
SN74HC74DR,U11,SOIC-14_3.9x8.7mm_P1.27mm,C6762,1
PAM8403D PAM8403DR,U12,SOIC-16_3.9x9.9mm_P1.27mm,C4990933,1
TLV6700DDCR,U14,SOT95P280X110-6N,C2868382,1
ABM8-272-T3,Y1,ABM8272T3,C20625731,1
